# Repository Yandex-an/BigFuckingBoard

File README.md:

# BigFuckingBoard
Контроллер 3D принтера на базе LPC1768. для работы с прошивками Marlin/klipper/RRF

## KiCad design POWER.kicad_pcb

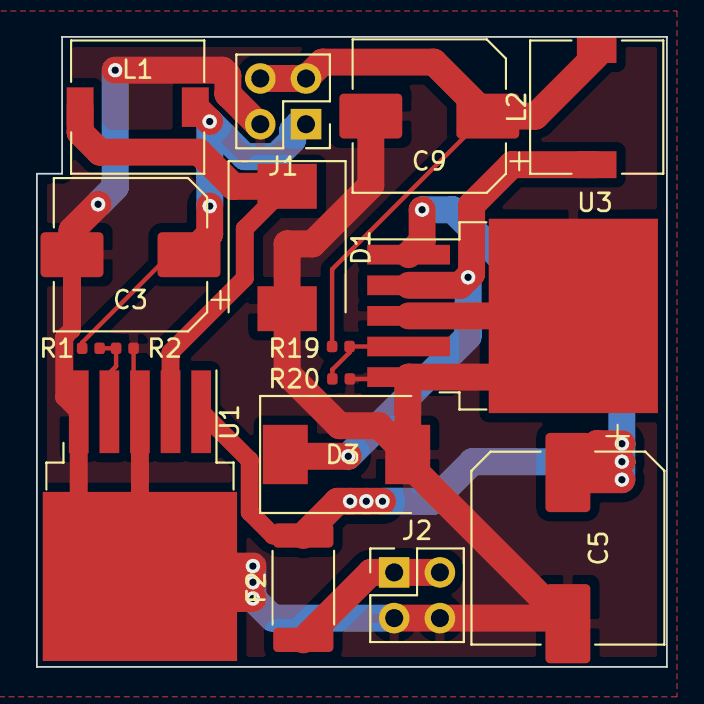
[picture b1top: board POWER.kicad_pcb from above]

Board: 2 copper layers, 35.0 x 35.0 mm, 16 parts (0 on the bottom side), 9 nets.

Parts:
C3, C9: 220uF; CP_Elec_8x10
C5: 470uF; CP_Elec_10x10.5
D1, D3: D; D_SMC
F2: 3A; Fuse_2512_6332Metric
J1, J2: Conn_02x02_Top_Bottom; PinHeader_2x02_P2.54mm_Vertical
L1, L2: 680mH; L_7.3x7.3_H3.5
R1: 6.2; R_0402_1005Metric
R2, R20: 1k; R_0402_1005Metric
R19: 3.3; R_0402_1005Metric
U1, U3: LM2596S-ADJ; TO-263-5_TabPin3

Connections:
+5V: C9.1, J1.3, J1.4, L2.2, R19.1
+9V: C3.1, J1.1, L1.2, R1.1
+VDC: F2.1, J2.1, J2.2
GND: C3.2, C5.2, C9.2, D1.2, D3.2, J1.2, J2.3, J2.4, R2.2, R20.2, U1.3, U1.5, U3.3, U3.5
unnamed: C5.1, F2.2, U1.1, U3.1
unnamed: D1.1, L1.1, U1.2
unnamed: D3.1, L2.1, U3.2
unnamed: R1.2, R2.1, U1.4
unnamed: R19.2, R20.1, U3.4

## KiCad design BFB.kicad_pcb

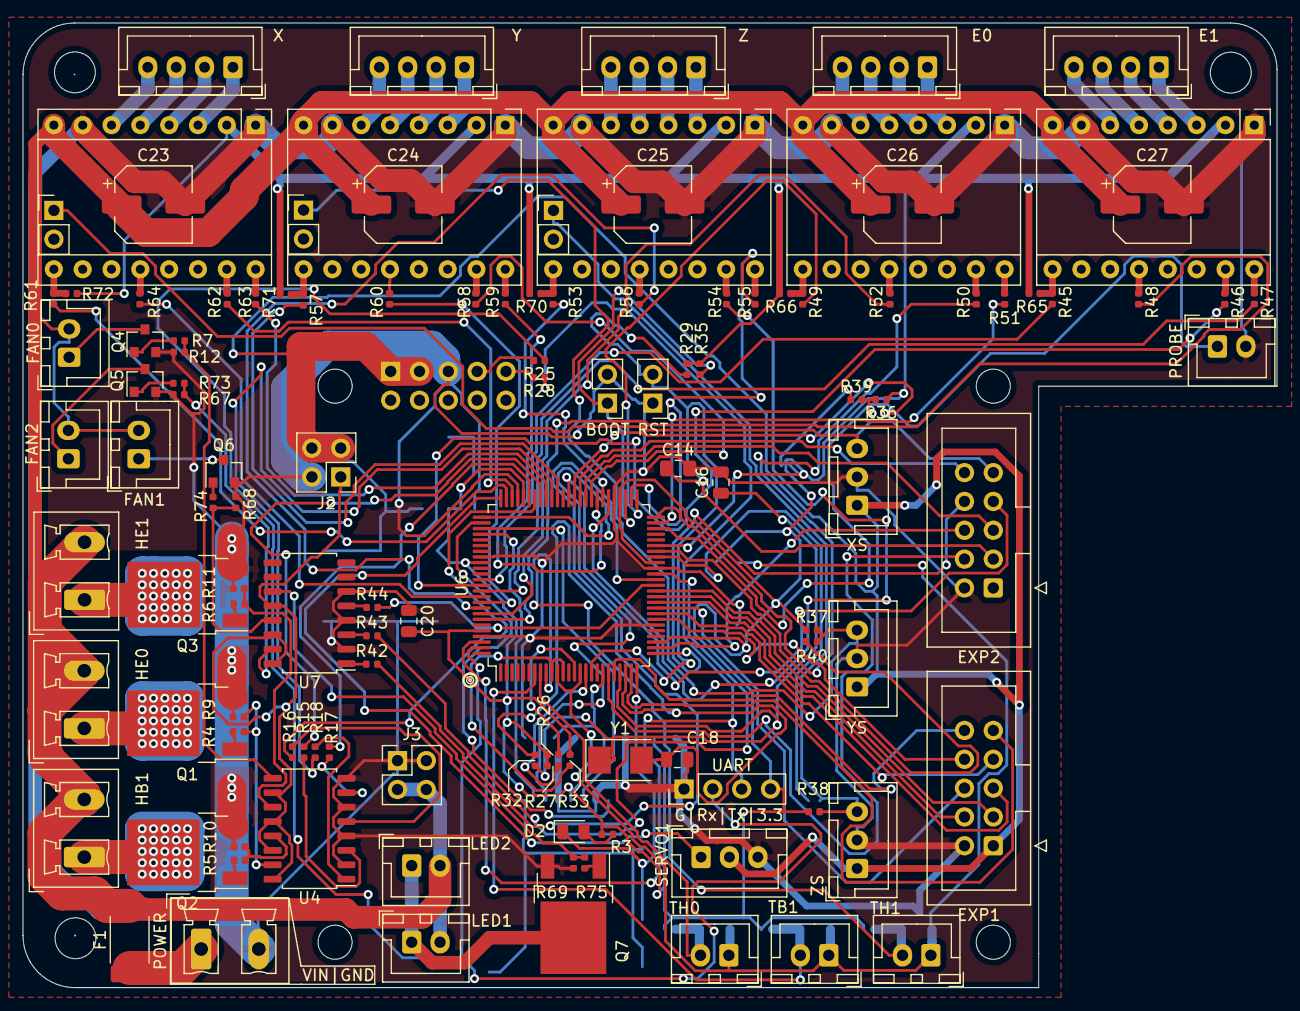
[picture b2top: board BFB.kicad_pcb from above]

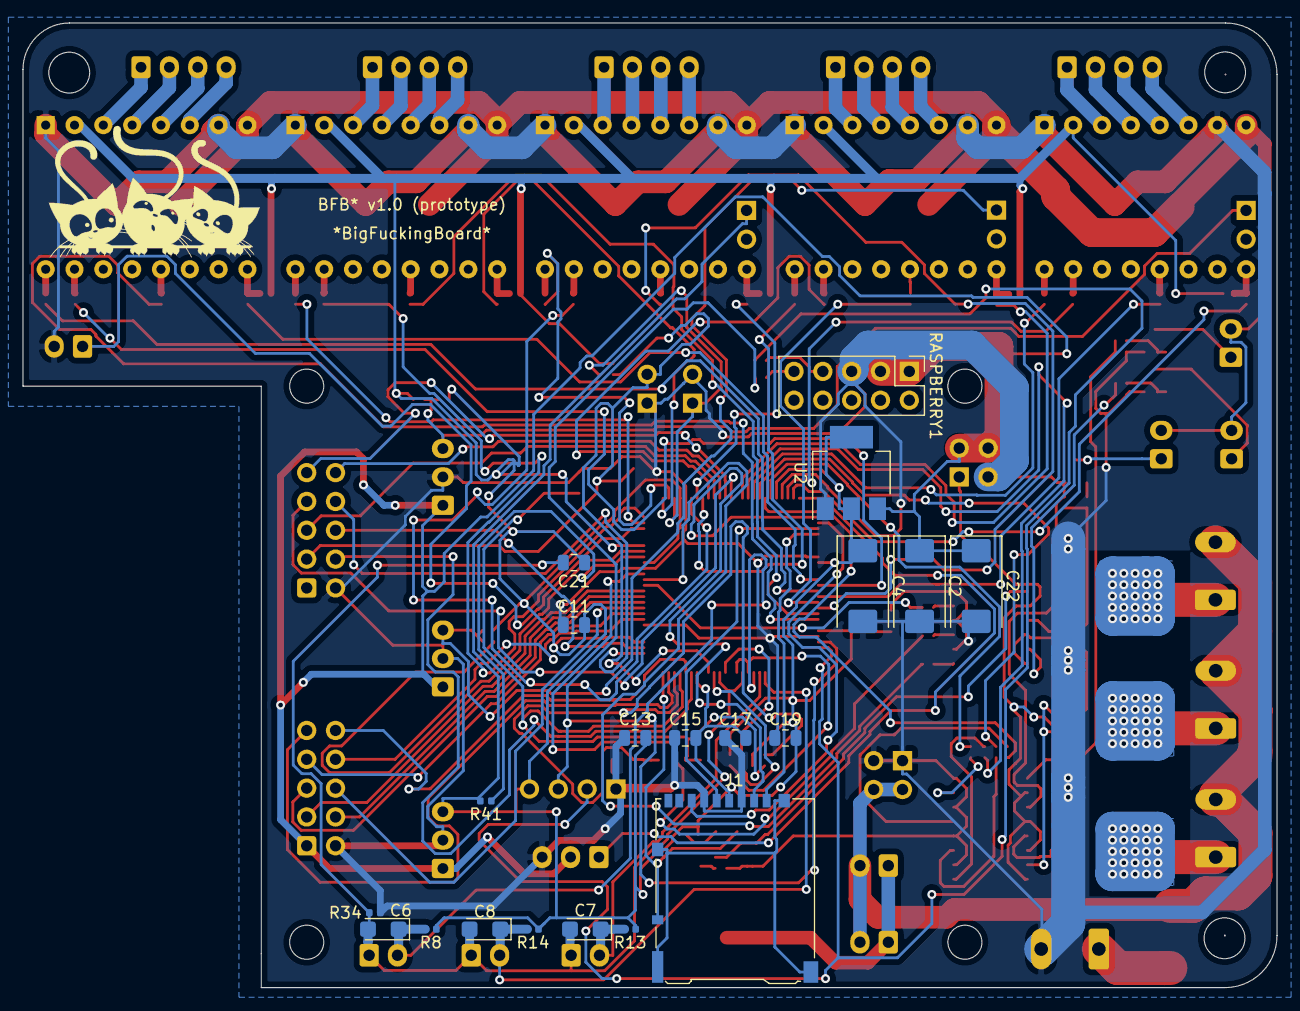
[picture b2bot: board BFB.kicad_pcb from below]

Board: 2 copper layers, 110.5 x 85.0 mm, 139 parts (20 on the bottom side), 145 nets.

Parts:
BOOT: Conn_01x02; PinHeader_1x02_P2.54mm_Vertical
C2, C4: CP; CP_EIA-7343-31_Kemet-D
C6, C7, C8: CP; CP_EIA-3216-12_Kemet-S
C11, C13, C15, C17, C19, C20, C21: 0.1uF; C_0805_2012Metric
C14: 18pF; C_0805_2012Metric_Pad1.15x1.40mm_HandSolder
C16, C18: 18pF; C_0805_2012Metric
C22: 22uF; CP_EIA-7343-31_Kemet-D
C23, C24, C25, C26, C27: CP; CP_Elec_6.3x5.3
D2: LED; LED_0805_2012Metric
E0, E1: Conn_01x04; JST_XH_B4B-XH-A_1x04_P2.50mm_Vertical
E0#2, E1#2: Pololu_Breakout_A4988; Pololu_Breakout-16_15.2x20.3mm
EXP1, EXP2: Conn_02x05_Odd_Even; IDC-Header_2x05_P2.54mm_Vertical
F1: Fuse; Fuse_2512_6332Metric_Pad1.52x3.35mm_HandSolder
FAN0, FAN1, FAN2: Conn_01x02; JST_XH_B2B-XH-A_1x02_P2.50mm_Vertical
HB1: Conn_01x02; PhoenixContact_MCV_1,5_2-G-5.08_1x02_P5.08mm_Vertical
HE0, HE1: Conn_01x02; PhoenixContact_MCV_1,5_2-G-5.08_1x02_P5.08mm_Vertical
J1: SD_Card; microSD_HC_Hirose_DM3AT-SF-PEJM5
J2, J3: Conn_02x02_Top_Bottom; PinHeader_2x02_P2.54mm_Vertical
LED1, LED2: Conn_01x02; JST_XH_B2B-XH-A_1x02_P2.50mm_Vertical
POWER: Conn_01x02; PhoenixContact_MCV_1,5_2-G-5.08_1x02_P5.08mm_Vertical
PROBE: Conn_01x02; JST_XH_B2B-XH-A_1x02_P2.50mm_Vertical
Q1, Q2, Q3: QM6006D; TO-252-2
Q4, Q5, Q6: BSS138; SOT-23
Q7: IRLZ44N; TO-252-2
R3, R39, R40, R41: 1k; R_0402_1005Metric
R4, R5, R6, R7, R73, R74, R75: 10R; R_0402_1005Metric
R8, R13: 4.7k; R_0402_1005Metric
R9, R10, R11, R12, R26, R27, R35, R36, R37, R38, R65, R66, R67, R68, R69, R70, R71, R72: 10k; R_0402_1005Metric
R14: 4,7k; R_0402_1005Metric
R15, R16, R17, R18, R42, R43, R44: 330R; R_0402_1005Metric
R25, R28, R45, R46, R47, R48, R49, R50, R51, R52, R53, R54, R55, R56, R57, R58, R59, R60, R61, R62, R63, R64: 100R; R_0402_1005Metric
R29: 10K; R_0402_1005Metric
R32: 1M; R_0402_1005Metric
R33, R34: 120R; R_0402_1005Metric
RASPBERRY1: Conn_02x05_Odd_Even; PinHeader_2x05_P2.54mm_Vertical
RST: Conn_01x02; PinHeader_1x02_P2.54mm_Vertical
SERVO1: Conn_01x03; JST_XH_B3B-XH-A_1x03_P2.50mm_Vertical
SHX: Conn_01x02; PinHeader_1x02_P2.54mm_Vertical
SHY1: Conn_01x02; PinHeader_1x02_P2.54mm_Vertical
SHZ1: Conn_01x02; PinHeader_1x02_P2.54mm_Vertical
TB1: Conn_01x02; JST_XH_B2B-XH-A_1x02_P2.50mm_Vertical
TH0, TH1: Conn_01x02; JST_XH_B2B-XH-A_1x02_P2.50mm_Vertical
U2: AMS1117-3.3; SOT-223-3_TabPin2
U4, U7: PC847; SOP-16_4.55x10.3mm_P1.27mm
U6: LPC1768FBD100; LQFP-100_14x14mm_P0.5mm
UART: Conn_01x04; PinHeader_1x04_P2.54mm_Vertical
X: Conn_01x04; JST_XH_B4B-XH-A_1x04_P2.50mm_Vertical
X1: Pololu_Breakout_A4988; Pololu_Breakout-16_15.2x20.3mm
XS: Conn_01x03; JST_XH_B3B-XH-A_1x03_P2.50mm_Vertical
Y: Conn_01x04; JST_XH_B4B-XH-A_1x04_P2.50mm_Vertical
Y1: 12MHz; Crystal_SMD_5032-2Pin_5.0x3.2mm
Y2: Pololu_Breakout_A4988; Pololu_Breakout-16_15.2x20.3mm
YS: Conn_01x03; JST_XH_B3B-XH-A_1x03_P2.50mm_Vertical
Z: Conn_01x04; JST_XH_B4B-XH-A_1x04_P2.50mm_Vertical
Z1: Pololu_Breakout_A4988; Pololu_Breakout-16_15.2x20.3mm
ZS: Conn_01x03; JST_XH_B3B-XH-A_1x03_P2.50mm_Vertical

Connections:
+3V3: C4.1, C11.2, C13.2, C15.2, C17.2, C19.2, C20.2, C21.1, E0#2.2, E1#2.2, J1.4, R3.1, R8.1, R13.1, R14.1, R26.2, R27.2, R29.2, R33.1, R35.1, R36.1, R37.1, R38.1, R65.1, R66.1, R70.1, R71.1, R72.1, U2.2, U6.19, U6.28, U6.42, U6.54, U6.71, U6.84, U6.96, UART.4, X1.2, Y2.2, Z1.2
+5V: C2.1, C22.1, EXP1.1, J2.3, J2.4, RASPBERRY1.1, RASPBERRY1.3, SERVO1.2, U2.3, XS.1, YS.1, ZS.1
+9V: J2.1, U4.10, U4.12, U4.14, U4.16, U7.12, U7.14, U7.16
+24V: F1.1, POWER.1
+VDC: C23.1, C24.1, C25.1, C26.1, C27.1, E0#2.8, E1#2.8, F1.2, FAN0.2, FAN1.2, FAN2.2, HB1.2, HE0.2, HE1.2, J3.3, J3.4, LED1.2, LED2.2, X1.8, Y2.8, Z1.8
GND: BOOT.2, C2.2, C4.2, C11.1, C13.1, C14.2, C15.1, C16.2, C17.1, C18.2, C19.1, C20.1, C22.2, C23.2, C24.2, C25.2, C26.2, C27.2, E0#2.1, E0#2.7, E1#2.1, E1#2.7, EXP1.2, EXP2.2, J1.3, J1.6, J2.2, J3.1, J3.2, POWER.2, PROBE.2, Q1.3, Q2.3, Q3.3, Q4.2, Q5.2, Q6.2, Q7.3, R9.2, R10.2, R11.2, R12.2, R34.1, R67.2, R68.2, R69.2, RASPBERRY1.5, RST.1, SERVO1.3, U2.1, U4.2, U4.4, U4.6, U4.8, U6.31, U6.41, U6.55, U6.72, U6.83, U6.97, U7.2, U7.4, U7.6, UART.1, X1.1, X1.7, XS.2, Y2.1, Y2.7, YS.2, Z1.1, Z1.7, ZS.2
GND1: C6.2, C7.2, C8.2, C21.2, R34.2, TB1.1, TH0.1, TH1.1, U6.11, U6.15
unnamed: BOOT.1, R35.2, U6.53
unnamed: C6.1, R8.2, TH1.2, U6.9
unnamed: C7.1, R13.2, TH0.2, U6.8
unnamed: C8.1, R14.2, TB1.2, U6.7
unnamed: C14.1, EXP2.3, R29.1, RST.2, U6.17
unnamed: C16.1, R32.2, U6.22, Y1.1
unnamed: C18.1, R32.1, U6.23, Y1.2
unnamed: D2.1, J1.10, U6.25
unnamed: D2.2, R3.2
unnamed: E0.1, E0#2.3
unnamed: E0.2, E0#2.4
unnamed: E0.3, E0#2.5
unnamed: E0.4, E0#2.6
unnamed: E0#2.9, R49.1, R66.2
unnamed: E0#2.12, R52.1
unnamed: E0#2.15, R50.1
unnamed: E0#2.16, R51.1
unnamed: E1.1, E1#2.3
unnamed: E1.2, E1#2.4
unnamed: E1.3, E1#2.5
unnamed: E1.4, E1#2.6
unnamed: E1#2.9, R45.1, R65.2
unnamed: E1#2.12, R48.1
unnamed: E1#2.15, R46.1
unnamed: E1#2.16, R47.1
unnamed: EXP1.3, U6.37
unnamed: EXP1.4, U6.36
unnamed: EXP1.5, U6.35
unnamed: EXP1.6, U6.34
unnamed: EXP1.7, U6.33
unnamed: EXP1.8, U6.32
unnamed: EXP1.9, U6.24
unnamed: EXP1.10, U6.21
unnamed: EXP2.4, U6.20
unnamed: EXP2.5, U6.60
unnamed: EXP2.6, U6.27
unnamed: EXP2.7, U6.63
unnamed: EXP2.8, U6.26
unnamed: EXP2.9, U6.62
unnamed: EXP2.10, U6.61
unnamed: FAN0.1, Q4.3
unnamed: FAN1.1, Q6.3
unnamed: FAN2.1, Q5.3
unnamed: HB1.1, Q2.2
unnamed: HE0.1, Q1.2
unnamed: HE1.1, Q3.2
unnamed: J1.1, U6.79
unnamed: J1.2, U6.76
unnamed: J1.5, U6.78
unnamed: J1.7, U6.77
unnamed: LED1.1, LED2.1, Q7.2
unnamed: PROBE.1, U6.48
unnamed: Q1.1, R4.1
unnamed: Q2.1, R5.1
unnamed: Q3.1, R6.1
unnamed: Q4.1, R7.1
unnamed: Q5.1, R73.1
unnamed: Q6.1, R74.1
unnamed: Q7.1, R75.1
unnamed: R4.2, R9.1, U4.15
unnamed: R5.2, R10.1, U4.13
unnamed: R6.2, R11.1, U4.11
unnamed: R7.2, R12.1, U4.9
unnamed: R15.1, U4.3
unnamed: R15.2, U6.68
unnamed: R16.1, U4.5
unnamed: R16.2, U6.69
unnamed: R17.1, U4.7
unnamed: R17.2, U6.70
unnamed: R18.1, U4.1
unnamed: R18.2, U6.66
unnamed: R25.1, U6.99, UART.2
unnamed: R25.2, RASPBERRY1.7
unnamed: R26.1, U6.14
unnamed: R27.1, U6.16
unnamed: R28.1, U6.98, UART.3
unnamed: R28.2, RASPBERRY1.9
unnamed: R33.2, U6.10, U6.12
unnamed: R36.2, R39.2, SHX.1, XS.3
unnamed: R37.2, R40.2, SHY1.1, YS.3
unnamed: R38.2, R41.2, SHZ1.1, ZS.3
unnamed: R39.1, U6.45
unnamed: R40.1, U6.44
unnamed: R41.1, U6.43
unnamed: R42.1, U7.1
unnamed: R42.2, U6.39
unnamed: R43.1, U7.3
unnamed: R43.2, U6.40
unnamed: R44.1, U7.5
unnamed: R44.2, U6.38
unnamed: R45.2, U6.87
unnamed: R46.2, U6.88
unnamed: R47.2, U6.89
unnamed: R48.2, U6.94
unnamed: R49.2, U6.51
unnamed: R50.2, U6.50
unnamed: R51.2, U6.49
unnamed: R52.2, U6.93
unnamed: R53.1, R70.2, Z1.9
unnamed: R53.2, U6.57
unnamed: R54.1, Z1.15
unnamed: R54.2, U6.56
unnamed: R55.1, Z1.16
unnamed: R55.2, U6.52
unnamed: R56.1, Z1.12
unnamed: R56.2, U6.92
unnamed: R57.1, R71.2, Y2.9
unnamed: R57.2, U6.65
unnamed: R58.1, Y2.15
unnamed: R58.2, U6.59
unnamed: R59.1, Y2.16
unnamed: R59.2, U6.58
unnamed: R60.1, Y2.12
unnamed: R60.2, U6.91
unnamed: R61.1, R72.2, X1.9
unnamed: R61.2, U6.74
unnamed: R62.1, X1.15
unnamed: R62.2, U6.73
unnamed: R63.1, X1.16
unnamed: R63.2, U6.67
unnamed: R64.1, X1.12
unnamed: R64.2, U6.90
unnamed: R67.1, R73.2, U7.15
unnamed: R68.1, R74.2, U7.13
unnamed: R69.1, R75.2, U7.11
unnamed: SERVO1.1, U6.75
unnamed: X.1, X1.3
unnamed: X.2, X1.4
unnamed: X.3, X1.5
unnamed: X.4, X1.6
unnamed: Y.1, Y2.3
unnamed: Y.2, Y2.4
unnamed: Y.3, Y2.5
unnamed: Y.4, Y2.6
unnamed: Z.1, Z1.3
unnamed: Z.2, Z1.4
unnamed: Z.3, Z1.5
unnamed: Z.4, Z1.6
